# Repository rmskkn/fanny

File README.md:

# Fanny — a USB PWM fan controller

A USB-controlled carrier board for an STM32F103C8T6 "Blue Pill" module. It
drives four 12 V PC fans and reads four analog sensors. The module shows up
on the host as a USB CDC serial port (`/dev/ttyACM*` or `COMx`).

## Key features

- **4 independent fan channels.** Each one switches between `pwm` (4-pin
  signal control) and `dc` (3-pin supply chopping) at runtime.
- **4 analog inputs** for NTC or voltage sensors plus 12 V rail sensing. All
  share one ADC scan with mV conversion.
- **Tach and stall detection** on all 4 channels. Fans 1-3 are counted by
  hardware timers, fan 4 by a level-checked interrupt.
- **Hardware failsafe by design.** Every control line rests in its "fan on"
  state by default, held there by pull resistors alone. A fan runs at
  100% on power-up, after a crash, or with the MCU pulled out. No firmware
  or host required.
- **Text protocol over USB CDC.** Comes with a Python CLI (`fanctl.py`) and
  a daemon (`fancontrold.py`) for temperature or GPU-temperature curves.

## Repository structure

```
.
├── firmware/          MCU firmware
│   ├── Core/          clocks, SysTick, linker script, board pin map
│   ├── Drivers/       libopencm3 submodule
│   ├── USB_DEVICE/    USB CDC-ACM device
│   ├── App/           fan, pwm, tach, protocol, thermal, safety
│   └── tests/         host-side unit tests
├── hardware/
│   ├── kicad/         schematic, symbol lib, board
│   ├── case/          3D-printed tray and cover (FreeCAD script, STEP, STL, renders)
│   ├── bom.csv        bill of materials
│   ├── pcb_3d.png     3D render of the placed board
│   ├── pcb_top.png    placement plot seen from the top
│   └── datasheets/    links to the key datasheets
└── host/              fanctl.py command-line client (pyserial)
```

## Prerequisites

KiCad 10.0.7, arm-none-eabi-gcc, OpenOCD, and Python 3 with pyserial:

```sh
# Arch
sudo pacman -S kicad arm-none-eabi-gcc arm-none-eabi-newlib openocd python python-pyserial

# Ubuntu 24.04
sudo add-apt-repository ppa:kicad/kicad-10.0-releases
sudo apt update
sudo apt install kicad gcc-arm-none-eabi openocd python3 python3-serial
```

You also need an ST-Link V2 programmer wired to the Blue Pill's SWD header
to flash firmware. FreeCAD 1.1 is only needed to change the printed case.

`make analyze` (clang static analyzer over the firmware, see Build below)
needs clang-23 specifically; a different major version can enable a
different default set of checkers, which has produced false positives on
this codebase before.

```sh
# Arch: clang already provides a clang-23 symlink, nothing extra to install
sudo pacman -S clang

# Ubuntu 24.04: its own archives don't carry clang-23, so use the LLVM
# project's own installer instead
wget https://apt.llvm.org/llvm.sh
chmod +x llvm.sh
sudo ./llvm.sh 23
```

## Hardware design

### Block overview

```mermaid
flowchart TB
    classDef power fill:#fde3d8,stroke:#e2572b,color:#111
    classDef usb fill:#dbe7ff,stroke:#2f6fed,color:#111
    classDef mcu fill:#e8d7f5,stroke:#5b4b8a,color:#111
    classDef pwm fill:#d7f5df,stroke:#2f9e44,color:#111
    classDef dcmode fill:#fdecc3,stroke:#c77f00,color:#111
    classDef tach fill:#d7f5df,stroke:#0f9b8e,color:#111
    classDef analog fill:#fbd9e8,stroke:#c2255c,color:#111

    subgraph PWR["Power 12 V"]
        PSU["12 V PSU"] --> J1["J1 Mate-N-Lok"] --> F1["F1 PTC 2.5A"] --> D2["D2 Schottky"] --> V12["+12V"]
        V12 --> FANV["fan +12V x4"]
        V12 --> DIV["10k/3.3k divider"] --> PB0["PB0 ADC"]
        V12 --> D3["D3 1N4148WT"] --> U1["U1 AMS1117-3.3"]
    end

    subgraph USB3V3["USB / 3V3"]
        USB["USB via Blue Pill microB"] --> P5V["+5V"] --> LDO["Blue Pill LDO"] --> V33["+3V3"] --> FB1["FB1"] --> V33A["+3V3A"]
        U1 --> V33
    end

    subgraph MCU["Blue Pill module on J2 and J3"]
        subgraph PWMSIG["PWM signal on fan pin 4"]
            TIM4["TIM4 PB6..PB9 25kHz"] --> BSS["BSS138 open drain"] --> FPWM["fan PWM pin"]
        end
        subgraph DCMODE["DC-mode motor switch per channel"]
            QINV["Q_inv BSS138"] --> QEN["Q_en gated by FANn_DCEN"] --> QPNP["Q_pnp AO3401A pull-up"] --> QHS["Q_hs AO3401A"] --> FSW["fan +12V motor switch"]
            GPIO["PA6 PA7 PA8 PB1 GPIO"] --> QEN
        end
        TIM4 -. reuses PWM signal .-> QINV
        subgraph TACHLANE["Tach"]
            FT["fan tach"] --> PU["10k pull-up"] --> RC["RC filter"] --> EXTI["TIM1/2/3 counters, EXTI PB15"]
        end
    end

    subgraph ANALOG["Analog inputs"]
        SENS["sensors"] --> RCB["1k + 100n + BAT54S"] --> ADC["PA0..PA3 ADC x4"]
    end

    class PSU,J1,F1,D2,V12,FANV,DIV,D3,U1 power
    class PB0 mcu
    class USB,P5V,LDO,V33,FB1,V33A usb
    class TIM4,BSS,FPWM pwm
    class QINV,QEN,QPNP,QHS,FSW,GPIO dcmode
    class FT,PU,RC,EXTI tach
    class SENS,RCB,ADC analog
```

### Pin map

| Function | Pins | Peripheral |
|---|---|---|
| Fan 1–4 PWM signal and the motor-switch chop signal in DC mode | PB6 PB7 PB8 PB9 | TIM4 CH1–4 at 25 kHz |
| Fan 1–4 DC-mode enable | PA6 PA7 PA8 PB1 | plain push-pull GPIO |
| Fan 1–3 tach | PA9 PA15 PB5 | TIM1 CH2, TIM2 CH1 (partial remap 1), TIM3 CH2 (partial remap), each in external clock mode counting falling edges in hardware |
| Fan 4 tach | PB15 | EXTI15 on both edges, counted only on a real high-to-low level change |
| AIN1–AIN4 | PA0–PA3 | ADC1 IN0–IN3 |
| 12 V sense | PB0 | ADC1 IN8 |

### Compatibility

Verified against the [Intel 4-wire PWM fan spec rev 1.2](https://www.konilabs.net/docs/standards/fan/intel_4wire_pwm_fans_specs_rev1_2.pdf):

| Spec requirement | Board implementation | Status |
|---|---|---|
| Pinout of GND then +12 V then tach then PWM | `Fan_4pin` header wired in that order | Match |
| PWM must be open-drain or open-collector with the fan pulling up | BSS138 open-drain transistor where the MCU only sinks | Match |
| PWM frequency between 21 kHz and 28 kHz with 25 kHz nominal | TIM4 at 72 MHz / 2880 which is exactly 25.000 kHz | Match |
| A released PWM line must run the fan at full speed | 100 kΩ pull-down holds the transistor off until firmware drives it | Match |
| Tach must be open-collector and pulled up at 2 pulses per rev | 10 kΩ pull-up to 3.3 V with `TACH_PULSES_PER_REV = 2` in firmware | Match |
| Tach pull-up rail of 5 V or less into a tolerant input | Pulled to 3.3 V. PA9, PA15 and PB15 are 5 V tolerant; PB5 is not, so fan 3 needs the 3.3 V pull-up | Match |

### Analog inputs (AIN1–AIN4)

Each input is a 3-pin header carrying 3V3A and SIG and GND. The conditioning
chain works like this:

- A 10 kΩ pull-up to 3V3A. Together with a 10 kΩ NTC to GND it forms a
  ratiometric temperature divider. Leave it unfitted for voltage-output
  sensors.
- A 1 kΩ series resistor and 100 nF to GND for anti-aliasing and sample
  charge.
- A BAT54S clamp to GND and 3V3A. PA0–PA3 are **not** 5 V tolerant.

The ADC references VDDA. The firmware measures VREFINT so it can report
millivolts corrected for the actual supply voltage.

#### Choosing an NTC

The on-board pull-up is 10 kΩ, matched to a 10 kΩ NTC with B=3950 (`ntc_r25 =
10000`, `ntc_beta = 3950` in the fan daemon config, both already the
defaults). Any bare 2-wire 10 kΩ/B3950 probe plugs straight in, SIG and GND,
no third wire needed — this is what the probe bundled with the
[Skip0ner 1X4L fan-1248 conf v1](https://skiponer.com/1x4l-pwm-fan-controller-manual/)
module is. Expected mV at a given temperature:
`hardware/datasheets/NTC-10k-B3950 Response Curve.md`, taken from the
10k/3950 column of Focusensing's
[10k thermistor reference chart](https://www.focusensing.com/10k-thermistor-chart-type-2-vs-type-3-vs-3950-tables_n196).
The onboard autocurve mode (`auto on`) uses the same table, baked into
`firmware/App/ntc_calib.h`. The firmware saves `auto on` or `auto off` to
flash with the curves, so a board that reboots without a host comes back in
the same mode.

A different R25 needs a matching pull-up swap, since the pull-up sets both
the divider's output range and the firmware's calibration constant: match
`ntc_r25` (host) and `ntc_calib_ain1..4` (firmware) to the new part's R25 and
B, and re-check `fanctl.py get`'s `ain N mv` against a known temperature
before trusting the curve.

### Power

- **12 V input:** a screw terminal, a PTC that holds 2.5 A, then an SS54
  Schottky diode (anode toward the PTC) that blocks a reversed supply instead
  of tripping the PTC. The PTC resets on its own, so a miswire leaves nothing
  to replace.
- **Module supply:** USB, 12 V, or both. The LDO on the Blue Pill makes
  3.3 V from USB VBUS. U1 (AMS1117-3.3) on the carrier makes 3.3 V from the
  12 V bus and feeds the module 3V3 pin, so the board runs with no USB cable.
  With both present, whichever regulator sits a little higher carries the
  load. D3 sits in front of U1 so that a USB-only board doesn't back-feed
  3.3 V onto the 12 V bus through U1.
- **12 V monitoring:** a 10 kΩ/3.3 kΩ divider into PB0. Full scale lands near
  13.3 V, so a supply above that reads as 13.3 V.
- **USB:** the micro-B connector of the Blue Pill and nothing else. The
  carrier has no USB connector or header or ESD protection of its own. The
  firmware pulls D+ low for 10 ms at boot to force the host to re-enumerate.

## BOM list

The full bill of materials is in [`hardware/bom.csv`](hardware/bom.csv).

## Case

[`hardware/case/`](hardware/case/) holds a two-part printed case: a low tray
and a cover. Both parts print without supports and weigh about 33 g together
in PLA.

The PCB screws onto four standoffs in the tray with M2x6 self-tapping screws.
Fit the MH4 screw before you plug in the Blue Pill, because the module covers
it. The tray wall stands 2 mm above the board, so the tray works on its own
too.

The cover sits on the tray wall, and a lip inside the wall holds it by
friction. Each fan header gets a window wide enough for a finger on the plug
latch. More windows sit over the sensor inputs, the 12 V input and the Blue
Pill SWD pins, and a notch in the side leaves room for the USB plug.

All sizes are constants at the top of `fan_controller_case.py`. After you
change one, rebuild the FreeCAD document, the STEP files and the STLs:

```sh
cd hardware/case
freecadcmd fan_controller_case.py
```

Run `freecad fan_controller_case.py` instead to also redraw the two images
above. The FreeCAD window opens for a few seconds and closes on its own.

The cover underside sits 20 mm above the PCB. That figure comes from an
estimated 18.6 mm Blue Pill stack with the BOOT jumpers fitted, so measure
your module and raise `TOP_CLEAR` if it stands taller.

## Firmware

### Build

```sh
git clone --recurse-submodules git@github.com:rmskkn/fanny.git
cd fanny
make                 # firmware/build/fanny.elf, .bin (~11.5 KiB flash)
make flash           # flash fanny.bin, OpenOCD + ST-Link over SWD
make test            # host-side protocol and conversion tests
make analyze         # clang static analyzer over the firmware sources
```

The first `make` builds libopencm3 for STM32F1 only. It also runs
`git submodule update --init` when the clone has no submodule checkout. The
same targets work from inside `firmware/`.

`make flash` wraps this OpenOCD call, with an ST-Link programmer on the
Blue Pill's SWD header. `fanny.bin` is a raw image with no load address, so
one is given on the command line, the start of flash on this MCU:

```sh
openocd -f interface/stlink.cfg -f target/stm32f1x.cfg \
    -c "program firmware/build/fanny.bin verify reset exit 0x08000000"
```

`fanny.elf` still builds alongside it (`make` keeps producing both), kept
for `arm-none-eabi-size` and debugging, but flashing only ever needs the bin.

### Failsafe behaviour

All fans run at 100 % whenever the controller is not in control and that holds
in both `pwm` and `dc` mode. Fan power comes straight from 12 V so this needs
nothing but 12 V present. The PWM signal line and the motor switch and the
DC-mode enable all rest in their "fan on" state. Pin 4 is released and
`R_gpd` holds the motor switch on and `R_dcen` holds the enable off. Either
mode reaches 100 % the same way.

| Case | Result |
|---|---|
| Power-up before the first command from the host, `auto off` saved | 100 % at reset, then the curve fallback below within 1 s |
| Power-up with `auto on` saved | Each fan follows its temperature curve from boot, with or without a host |
| USB unplugged or host powered off, `auto on` | Module stays powered from 12 V through U1 and keeps driving each fan from its temperature curve |
| USB unplugged or host powered off, `auto off` | Module stays powered from 12 V through U1, gets no commands, and after 20 s falls back to the curves as in the last row |
| Module pulled out of its socket | Both switches rest on at 100 % |
| Supply sags below the reset threshold of the STM32 near 1.9 V | MCU held in reset and both switches rest on at 100 % |
| Firmware hangs | Watchdog resets the MCU after 1 s and both switches rest on during reset at 100 % |
| No valid command for 20 s while the module is still powered and `auto off` | Firmware failsafe sets 100 %, the LED blinks fast and the mode stays unchanged. Within 1 s each fan falls back to its saved curve. A channel with no curve or a bad sensor stays at 100 %, and a corrupted curve on any channel keeps every fan at 100 %. The next valid command hands control back to the host |

Running `fanctl.py watch` or a control daemon keeps the 20 s timer from
expiring. A fan is flagged `stall=1` when its duty sits above 0 but its tach
reads 0 RPM for 3 s. Fans without a tach wire always show this flag.

### Host commands

The protocol is text over USB CDC and the baud rate is ignored. Each command
is one line ending in `\n` and each reply ends with `ok` or `err <reason>`.

```
> set 2 40          duty 0..100 for fan 1..4 or "all"
ok
> mode 3 dc         pwm (4-pin) | dc (3-pin)
ok
> get
fan 1 mode=pwm duty=100 rpm=1590 stall=0
fan 2 mode=pwm duty=40 rpm=780 stall=0
fan 3 mode=dc duty=100 rpm=1200 stall=0
fan 4 mode=pwm duty=100 rpm=0 stall=1
ain 1 raw=2047 mv=1649
...
v12 mv=12043
vdda mv=3302
mcu temp=31.4
failsafe=0
ok
> ping              keepalive
ok
```

## Host tool

```sh
pip install -r host/requirements.txt
python3 host/fanctl.py -p /dev/ttyACM0 get
python3 host/fanctl.py set all 50
python3 host/fanctl.py mode 3 dc
python3 host/fanctl.py watch -i 2
```

### Setting one fan

Use the fan number from 1 to 4 in place of `all`. Fan 1 is header J5 and fan
4 is header J8.

```sh
python3 host/fanctl.py set 1 50      # fan 1 to 50 %
python3 host/fanctl.py set 3 80      # fan 3 to 80 %
python3 host/fanctl.py set 4 0       # fan 4 to 0 % (some fans keep turning slowly)
python3 host/fanctl.py -p /dev/ttyACM1 set 2 40   # board on another port
```

- Each command sets one fan or all fans. Lists such as `1,2` and ranges such
  as `1-3` are not accepted.
- To check a fan run `python3 host/fanctl.py get` and read the
  `fan N mode=... duty=... rpm=...` line.
- With `auto off`, settings hold only while the host keeps talking to the
  board. When no command arrives for 20 s the fans fall back to the saved
  curves, or 100 % without them. Keep `fanctl.py watch` or a control daemon
  running to hold the values.
- `mode <1-4|all> pwm|dc` picks the speed-control path for a channel: `pwm`
  for a 4-pin fan, `dc` for a 3-pin fan. It falls back to `pwm` at every
  boot and after every reconnect so the channel of a 3-pin fan needs
  `mode N dc` sent again each time.

The `FanController` class in `fanctl.py` can be imported to build a control
daemon. One example is a daemon that maps an NTC reading from `ain` onto a fan
duty. For a 10 kΩ NTC sitting on the 10 kΩ bias resistor the resistance is
R<sub>NTC</sub> = 10 kΩ × mV / (VDDA − mV).

### Fan control daemon

`host/fancontrold.py` is exactly that daemon. It reads an INI config shown in
`host/fancontrol.conf.example`. The config can set each of the four channels
to a constant duty or to a temperature curve driven by one AIN input or to a
curve driven by the temperature of an NVIDIA GPU through `sensor = gpuN` read
via `nvidia-smi` using the higher of the core and memory temperature. A
managed channel also takes `type = pwm` for the 4-pin default or `type = dc`
for a 3-pin fan. The daemon sends `mode` once at startup and again after every
reconnect because a firmware reset returns every channel to `pwm`. It sends
`auto off` at the same points, because the board ignores `set` while `auto on`
runs. Stopping the daemon leaves the board in `auto off`, so run
`fanctl.py auto on` to hand control back to the board. Every cycle
it re-sends the duty of each managed channel which doubles as the ping that
holds off the 20 s firmware failsafe. A channel with no `[fanN]` section is
left alone. `nvidia-smi` must be on `PATH` and no extra Python dependency is
needed.

For a `gpuN` sensor install the proprietary NVIDIA driver which provides
`nvidia-smi`:

```sh
# Arch
sudo pacman -S nvidia nvidia-utils

# Ubuntu 24.04
sudo apt install nvidia-driver-550
```

Reboot the machine to load the nvidia modules. Verify with
`nvidia-smi --query-gpu=index,temperature.gpu,temperature.memory --format=csv`.

```sh
cp host/fancontrol.conf.example ~/.config/fancontrol.conf
# edit ~/.config/fancontrol.conf for your sensors and curves
python3 host/fancontrold.py                 # foreground, Ctrl-C to stop
```

To run it as a systemd user service:

```sh
mkdir -p ~/.config/systemd/user
cp host/systemd/fancontrold.service ~/.config/systemd/user/
# edit ExecStart in that file to this repo's checkout path
systemctl --user daemon-reload
systemctl --user enable --now fancontrold.service
loginctl enable-linger "$USER"   # only if the board must run with no user session logged in
```

### Updating firmware via USB

A fresh board's first flash still needs SWD: `make ota_fw` builds the
bootloader and app, `make flash_ota` writes the app part at its fixed
address (the bootloader itself has no `make` target yet, so it still
needs its own manual OpenOCD `program` command). From there, every
later update goes over the same USB CDC link, no SWD needed.

```sh
python3 host/fwtool.py flash firmware/build/fanny_app.bin -v 2
```

This sends `update` to the running app, which reboots into the bootloader.
The bootloader erases the app region, writes the new image, checks its
SHA-256, and boots it. `-v` sets the version number sealed into the image;
bump it on every release. To build the sealed image without flashing it:

```sh
python3 host/fwtool.py build firmware/build/fanny_app.bin -v 2 -o update.img
```

The image format `fwtool.py` builds, and the bootloader checks, comes from
the `firmware/Bootloader/chunky` submodule
([rmskkn/chunky_mcu_updater](https://github.com/rmskkn/chunky_mcu_updater)).

## Known limits

- **0 % doesn't stop every 4-pin fan in `pwm` mode** (fan-dependent). It does
  stop the fan in `dc` mode.
- **Duty 1-100 % maps to 10-100 % on the PWM line.** A Noctua NF-P12 PWM
  won't start below 10 % and stops below about 6 % even after a spin-up, so
  the firmware never sends less than 10 % unless you set 0 %. At 1 % that fan
  runs at about 200 rpm. Every other setting lands a little above its raw
  value: 50 % sends 55 %.
- **3-pin fans in `dc` mode won't start below ~30-40 % duty** (motor limit,
  not firmware). Set a curve minimum above it.
- **Fan 4 tach uses an interrupt, not a hardware counter.** Each counter
  needs a whole timer, and the STM32F103C8 has four: TIM1-TIM3 count fans
  1-3 and TIM4 makes the PWM. Fan 4 runs on EXTI15 with a pin-level check
  that ignores spikes shorter than the interrupt entry time (about 0.5 us).
  Longer glitches still count, and edges closer together than the handler
  runtime can merge.
- **JTAG is off** because fan 2 tach uses PA15. SWD on PA13/PA14 still
  flashes and debugs the board.
- **Tach under-reads in `dc` mode** since the fan is unpowered during the
  chopped-off phase. `stall` is only meaningful near 100 % duty.
- **25 kHz chop stresses a fan's input cap** but stays inaudible. All four
  `pwm` channels share one chop frequency.

## Special thanks

These open-source projects helped build the project:

1. [KiCAD-MCP-Server](https://github.com/mixelpixx/KiCAD-MCP-Server) by
   mixelpixx drives KiCad schematic and PCB edits over MCP.
2. [freecad-mcp](https://github.com/neka-nat/freecad-mcp) by neka-nat drives
   FreeCAD over MCP for the printed case.
3. [KiCadRoutingTools](https://github.com/drandyhaas/KiCadRoutingTools) by
   drandyhaas reroutes nets that fail DRC.

## License

Copyright © 2026 Roman Skakun.

The hardware and the code use different licenses.

The hardware design files in `hardware/` (KiCad project, BOM, renders, and
the case model files) are licensed under
[Creative Commons Attribution-NonCommercial-ShareAlike 4.0 International](LICENSE)
(CC BY-NC-SA 4.0). You may build, modify and share the design for personal
and other non-commercial purposes, with attribution and under the same
license. Commercial use needs a separate written license from the copyright
holder. That includes selling assembled boards, bare PCBs or kits.

The 3D models in `hardware/kicad/3dmodels/` are copied from the KiCad
library and keep their own CC-BY-SA 4.0 license with the KiCad libraries
exception. See [`hardware/kicad/3dmodels/README.md`](hardware/kicad/3dmodels/README.md).

The code in `firmware/`, `host/`, `scripts/`, `hardware/scripts/` and the
case generator `hardware/case/fan_controller_case.py` is licensed under the [GNU General Public License v3.0](LICENSE-GPL-3.0). You
may use, change and redistribute it, including commercially, as long as you
release the source of every version you distribute under the same license.

`firmware/Drivers/libopencm3` is a submodule under its own LGPL-3.0 license
and is covered by neither of the above.

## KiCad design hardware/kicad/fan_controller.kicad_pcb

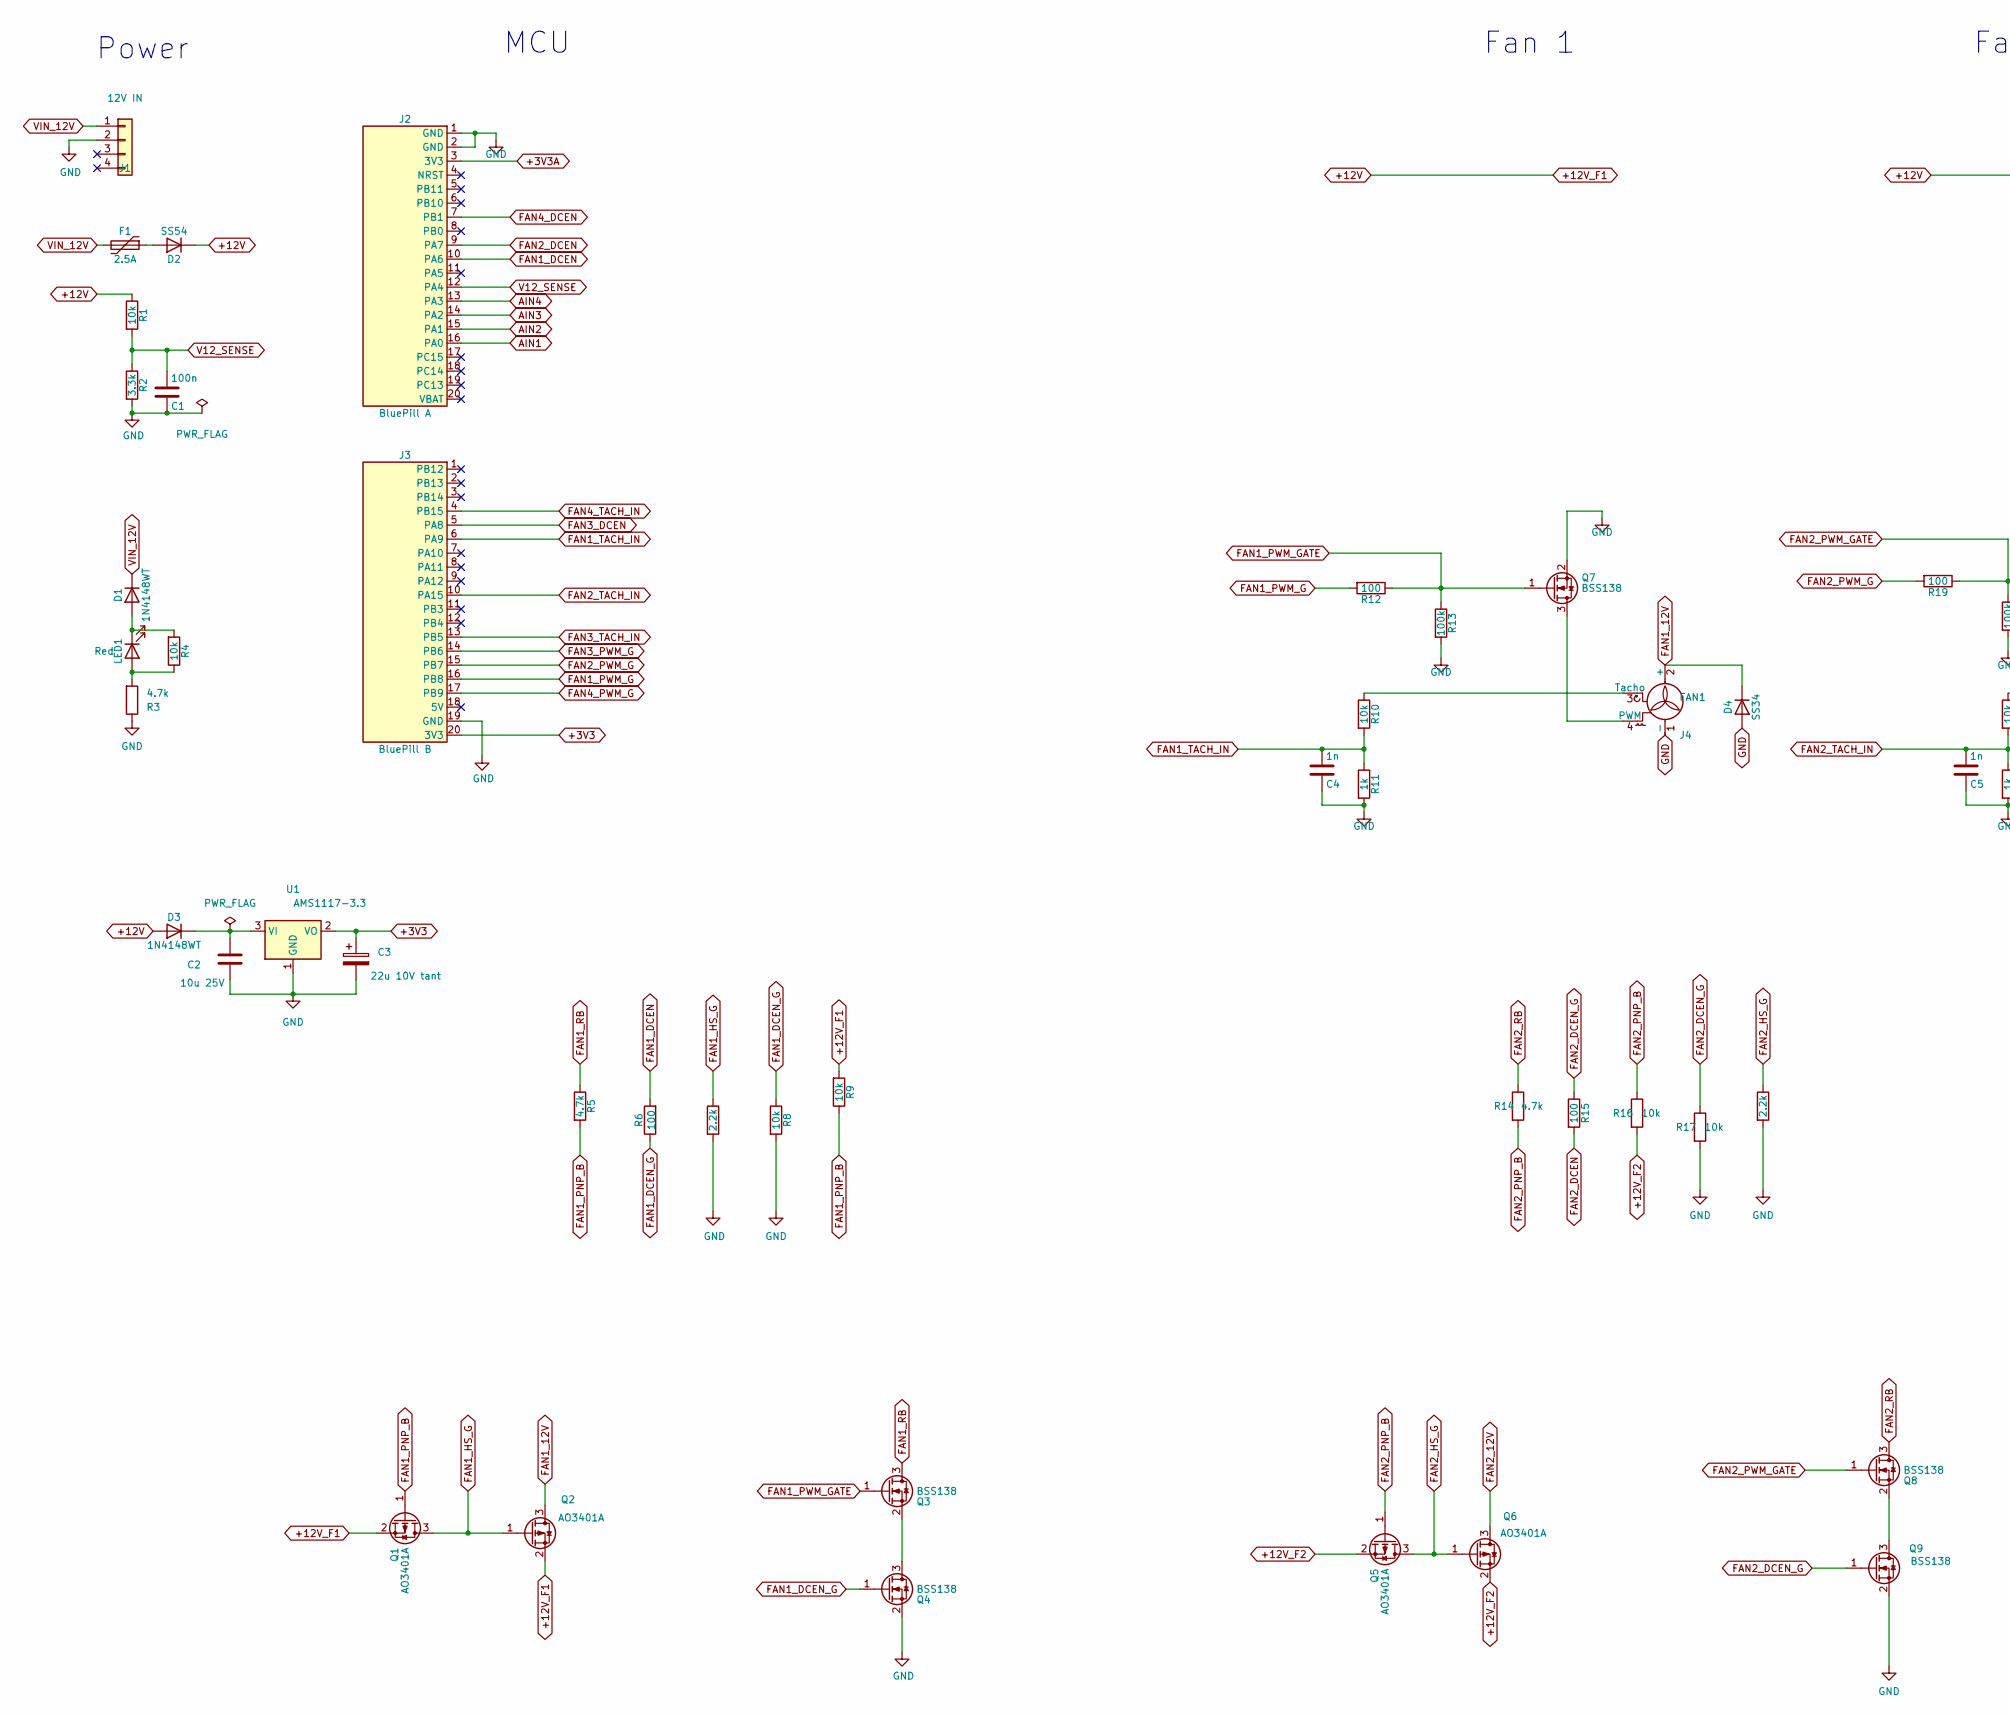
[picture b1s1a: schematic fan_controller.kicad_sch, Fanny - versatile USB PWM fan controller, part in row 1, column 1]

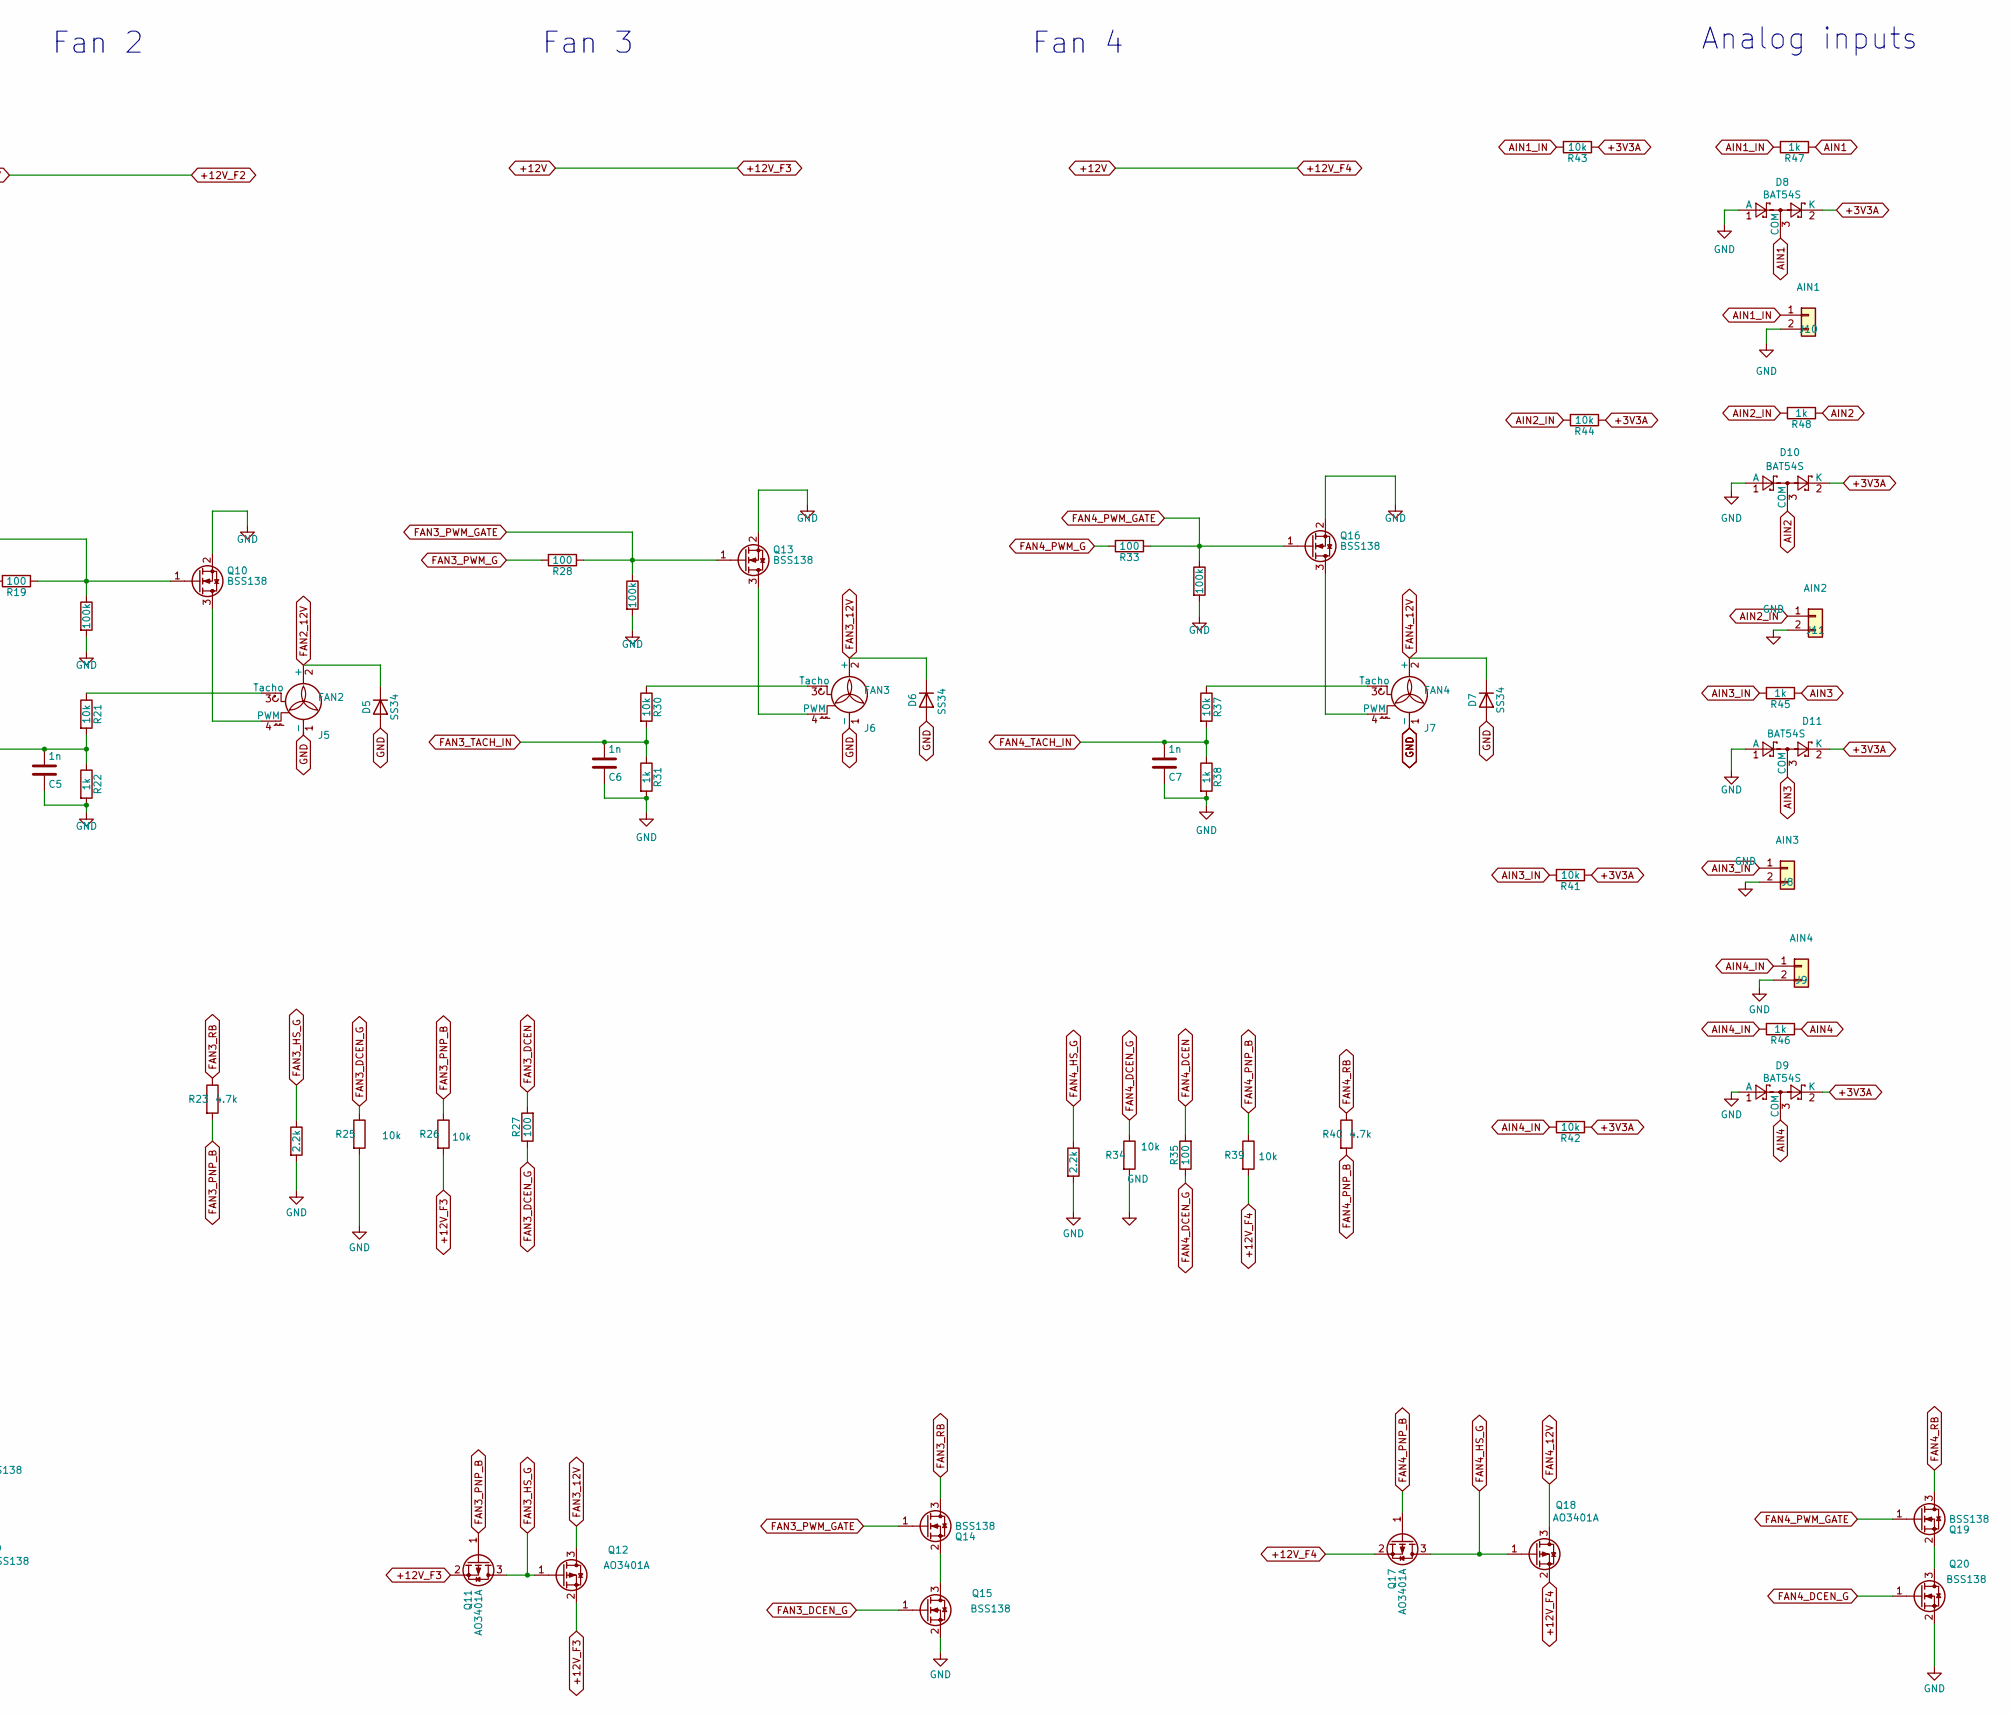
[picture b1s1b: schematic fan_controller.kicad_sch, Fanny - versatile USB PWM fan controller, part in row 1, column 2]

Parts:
C1: 100n; C_0603_1608Metric
C2: 10u 25V; C_0805_2012Metric
C3: 22u 10V tant; CP_EIA-3216-18_Kemet-A
C4, C5, C6, C7: 1n; C_0603_1608Metric
D1, D3: 1N4148WT; D_SOD-523
D2: SS54; D_SMB; MPN Littelfuse SMBJ13A
D4, D5, D6, D7: SS34; D_SMA; MPN SS34
D8, D9, D10, D11: BAT54S; SOT-23; MPN Nexperia BAT54S,215
F1: 2.5A; Fuse_1812_4532Metric; MPN Bourns MF-MSMF250/16X-2
J1: 12V IN; ConnHeader_MateNLok_1x04_P5.08mm_Vertical; MPN TE Connectivity 350424-1
J2: BluePill A; PinSocket_1x20_P2.54mm_Vertical
J3: BluePill B; PinSocket_1x20_P2.54mm_Vertical
J4: FAN1; FanPinHeader_1x04_P2.54mm_Vertical; MPN Molex 47053-1000
J5: FAN2; FanPinHeader_1x04_P2.54mm_Vertical; MPN Molex 47053-1000
J6: FAN3; FanPinHeader_1x04_P2.54mm_Vertical; MPN Molex 47053-1000
J7: FAN4; FanPinHeader_1x04_P2.54mm_Vertical; MPN Molex 47053-1000
J8: AIN3; JST_PH_B2B-PH-K_1x02_P2.00mm_Vertical
J9: AIN4; JST_PH_B2B-PH-K_1x02_P2.00mm_Vertical
J10: AIN1; JST_PH_B2B-PH-K_1x02_P2.00mm_Vertical
J11: AIN2; JST_PH_B2B-PH-K_1x02_P2.00mm_Vertical
LED1: Red; LED_0603_1608Metric
Q1, Q2, Q5, Q6, Q11, Q12, Q17, Q18: AO3401A; SOT-23; MPN Alpha & Omega AO3401A
Q3, Q7, Q8, Q10, Q13, Q14, Q16, Q19: BSS138; SOT-23; MPN onsemi BSS138
Q4, Q9, Q15, Q20: BSS138; SOT-23
R1, R4, R8, R9, R10, R16, R17, R21, R25, R26, R30, R34, R37, R39, R41, R42, R43, R44: 10k; R_0603_1608Metric
R2: 3.3k; R_0603_1608Metric
R3: 4.7k; R_1206_3216Metric
R5, R14, R23, R40: 4.7k; R_0603_1608Metric
R6, R12, R15, R19, R27, R28, R33, R35: 100; R_0603_1608Metric
R7, R18, R24, R32: 2.2k; R_0603_1608Metric
R11, R22, R31, R38, R45, R46, R47, R48: 1k; R_0603_1608Metric
R13, R20, R29, R36: 100k; R_0603_1608Metric
U1: AMS1117-3.3; SOT-223-3_TabPin2

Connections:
+3V3: C3.1, J3.20 (3V3), U1.2 (VO); also elsewhere on the board
+3V3A: D8.2 (K), D9.2 (K), D10.2 (K), D11.2 (K), J2.3 (3V3), R41.1, R42.1, R43.1, R44.1; also elsewhere on the board
+12V: D2.1 (K), D3.2 (A), Q1.2 (S), Q2.2 (S), Q5.2 (S), Q6.2 (S), Q11.2 (S), Q12.2 (S), Q17.2 (S), Q18.2 (S), R1.1, R9.2, R16.2, R26.2, R39.2
AIN1: D8.3 (COM), J2.16 (PA0), R47.1
AIN1_IN: J10.1, R43.2, R47.2
AIN2: D10.3 (COM), J2.15 (PA1), R48.1
AIN2_IN: J11.1, R44.2, R48.2
AIN3: D11.3 (COM), J2.14 (PA2), R45.1
AIN3_IN: J8.1, R41.2, R45.2
AIN4: D9.3 (COM), J2.13 (PA3), R46.1
AIN4_IN: J9.1, R42.2, R46.2
FAN1_12V: D4.1 (K), J4.2 (+), Q2.3 (D)
FAN1_DCEN: J2.10 (PA6), R6.2
FAN1_DCEN_G: Q4.1 (G), R6.1, R8.1
FAN1_HS_G: Q1.3 (D), Q2.1 (G), R7.1
FAN1_PNP_B: Q1.1 (G), R5.2, R9.1
FAN1_PWM_G: J3.16 (PB8), R12.2
FAN1_PWM_GATE: Q3.1 (G), Q7.1 (G), R12.1, R13.1
FAN1_RB: Q3.3 (D), R5.1
FAN1_TACH_IN: C4.1, J3.6 (PA9), R10.2, R11.1
FAN2_12V: D5.1 (K), J5.2 (+), Q6.3 (D)
FAN2_DCEN: J2.9 (PA7), R15.2
FAN2_DCEN_G: Q9.1 (G), R15.1, R17.1
FAN2_HS_G: Q5.3 (D), Q6.1 (G), R18.1
FAN2_PNP_B: Q5.1 (G), R14.2, R16.1
FAN2_PWM_G: J3.15 (PB7), R19.2
FAN2_PWM_GATE: Q8.1 (G), Q10.1 (G), R19.1, R20.1
FAN2_RB: Q8.3 (D), R14.1
FAN2_TACH_IN: C5.1, J3.10 (PA15), R21.2, R22.1
FAN3_12V: D6.1 (K), J6.2 (+), Q12.3 (D)
FAN3_DCEN: J3.5 (PA8), R27.2
FAN3_DCEN_G: Q15.1 (G), R25.1, R27.1
FAN3_HS_G: Q11.3 (D), Q12.1 (G), R24.1
FAN3_PNP_B: Q11.1 (G), R23.2, R26.1
FAN3_PWM_G: J3.14 (PB6), R28.2
FAN3_PWM_GATE: Q13.1 (G), Q14.1 (G), R28.1, R29.1
FAN3_RB: Q14.3 (D), R23.1
FAN3_TACH_IN: C6.1, J3.13 (PB5), R30.2, R31.1; also elsewhere on the board
FAN4_12V: D7.1 (K), J7.2 (+), Q18.3 (D)
FAN4_DCEN: J2.7 (PB1), R35.2
FAN4_DCEN_G: Q20.1 (G), R34.1, R35.1
FAN4_HS_G: Q17.3 (D), Q18.1 (G), R32.1
FAN4_PNP_B: Q17.1 (G), R39.1, R40.2
FAN4_PWM_G: J3.17 (PB9), R33.2
FAN4_PWM_GATE: Q16.1 (G), Q19.1 (G), R33.1, R36.1
FAN4_RB: Q19.3 (D), R40.1
FAN4_TACH_IN: C7.1, J3.4 (PB15), R37.2, R38.1; also elsewhere on the board
GND: C1.2, C2.2, C3.2, C4.2, C5.2, C6.2, C7.2, D4.2 (A), D5.2 (A), D6.2 (A), D7.2 (A), D8.1 (A), D9.1 (A), D10.1 (A), D11.1 (A), J1.2, J2.1 (GND), J2.2 (GND), J3.19 (GND), J4.1 (-), J5.1 (-), J6.1 (-), J7.1 (-), J8.2, J9.2, J10.2, J11.2, Q4.2 (S), Q7.2 (S), Q9.2 (S), Q10.2 (S), Q13.2 (S), Q15.2 (S), Q16.2 (S), Q20.2 (S), R2.2, R3.1, R7.2, R8.2, R11.2, R13.2, R17.2, R18.2, R20.2, R22.2, R24.2, R25.2, R29.2, R31.2, R32.2, R34.2, R36.2, R38.2, U1.1 (GND); also elsewhere on the board
unnamed: D1.2 (A), LED1.1 (K), R4.2
unnamed: D2.2 (A), F1.1
unnamed: C2.1, D3.1 (K), U1.3 (VI)
unnamed: J4.4 (PWM), Q7.3 (D)
unnamed: J4.3 (Tacho), R10.1
unnamed: J5.4 (PWM), Q10.3 (D)
unnamed: J5.3 (Tacho), R21.1
unnamed: J6.4 (PWM), Q13.3 (D)
unnamed: J6.3 (Tacho), R30.1
unnamed: J7.4 (PWM), Q16.3 (D)
unnamed: J7.3 (Tacho), R37.1
unnamed: LED1.2 (A), R3.2, R4.1
unnamed: Q3.2 (S), Q4.3 (D)
unnamed: Q8.2 (S), Q9.3 (D)
unnamed: Q14.2 (S), Q15.3 (D)
unnamed: Q19.2 (S), Q20.3 (D)
V12_SENSE: C1.1, J2.12 (PA4), R1.2, R2.1
VIN_12V: D1.1 (K), F1.2, J1.1

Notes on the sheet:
Analog inputs
Power
Fan 3
MCU
Fan 2
Fan 1
Fan 4

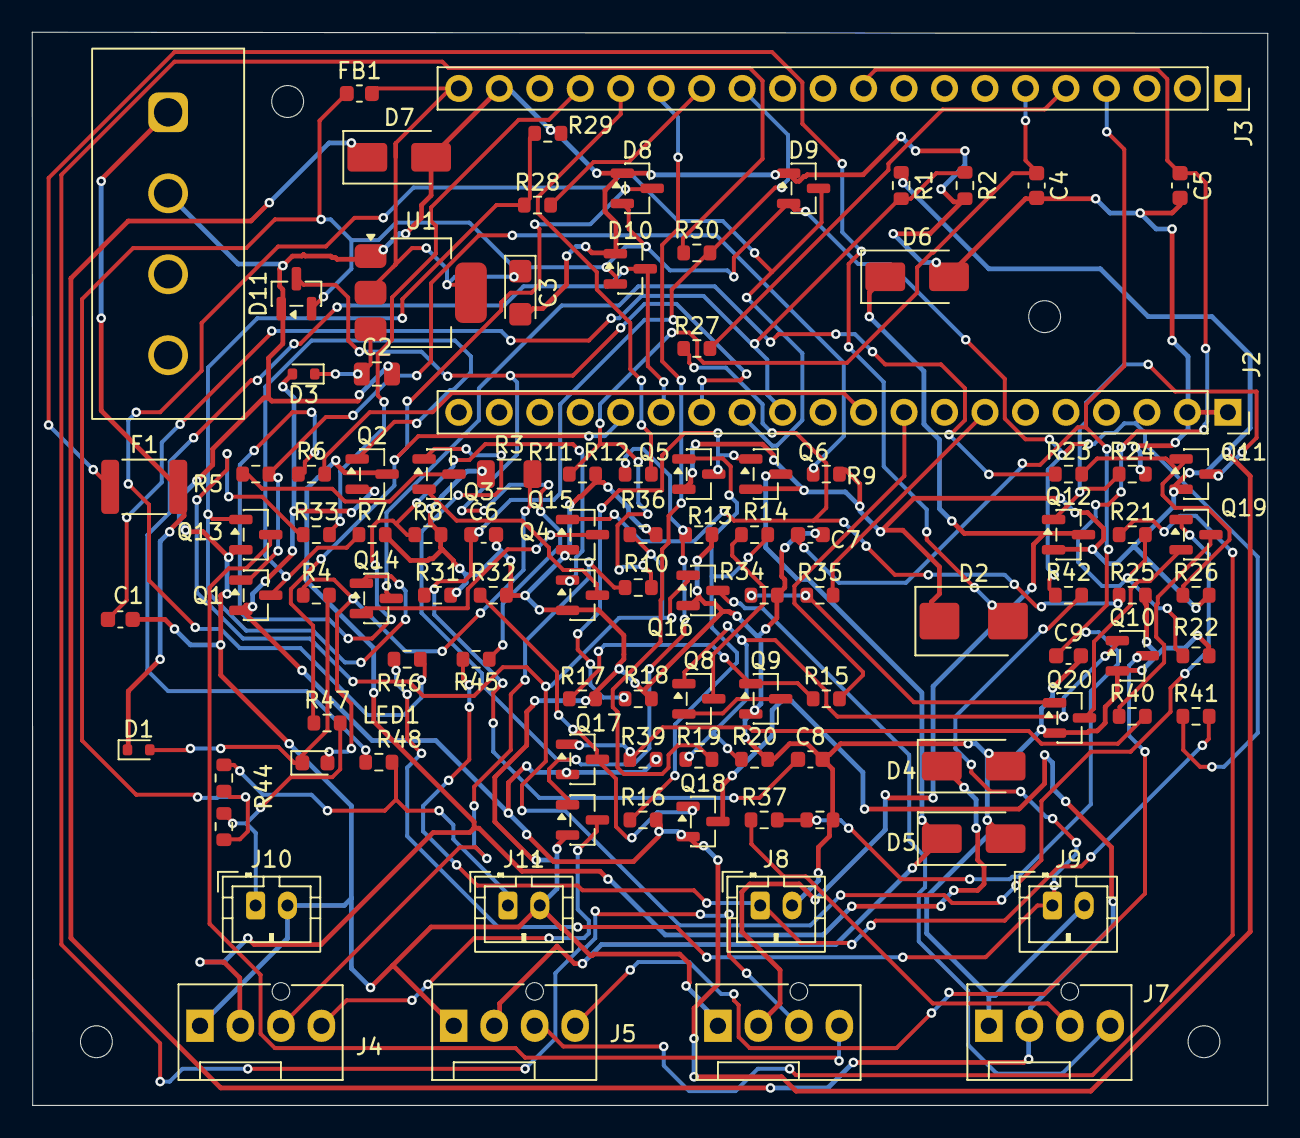
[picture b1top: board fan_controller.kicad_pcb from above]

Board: 2 copper layers, 77.5 x 67.3 mm, 107 parts (0 on the bottom side), 66 nets.

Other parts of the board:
C8, C9: 1n; C_0603_1608Metric
FB1: 600R@100MHz; L_0603_1608Metric
MH1, MH2, MH3, MH4: MountingHole_2mm

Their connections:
+3V3: FB1.2; also elsewhere on the board
+3V3A: FB1.1; also elsewhere on the board
FAN3_TACH_IN: C8.1; also elsewhere on the board
FAN4_TACH_IN: C9.1; also elsewhere on the board
GND: C8.2, C9.2; also elsewhere on the board

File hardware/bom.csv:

Qty,References,Value,Footprint,MPN (example),DigiKey PN,DigiKey URL,Notes,DNP
1,C1,100n,C_0603_1608Metric,Yageo CC0603KRX7R9BB104,311-1344-2-ND,https://www.digikey.com/en/products/detail/yageo/CC0603KRX7R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,,
4,C4 C5 C6 C7,1n,C_0603_1608Metric,Yageo CC0603KRX7R9BB102,311-1080-2-ND,https://www.digikey.com/en/products/detail/yageo/CC0603KRX7R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,,
1,C2,10u 25V,C_0805_2012Metric,Yageo CC0805KKX5R8BB106,311-1869-2-ND,https://www.digikey.com/en/products/detail/yageo/CC0805KKX5R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,U1 input cap,
1,C3,22u 10V tant,CP_EIA-3216-18_Kemet-A,KYOCERA AVX TAJA226K010RNJ,478-1663-2-ND,https://www.digikey.com/en/products/detail/kyocera-avx/TAJA2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,U1 output cap; tantalum per AMS1117 datasheet stability note,
1,D2,SS54,D_SMB,Shenzhen Slkormicro Semicon SS54B,5399-SS54BCT-ND,https://www.digikey.com/en/products/detail/shenzhen-slkormic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,Schottky now (reverse-polarity block); was SMBJ13A TVS,
4,D4 D5 D6 D7,SS34,D_SMA,SMC Diode Solutions SS34AF,1655-SS34AFTR-ND,https://www.digikey.com/en/products/detail/smc-diode-solutio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,,
4,D8 D9 D10 D11,BAT54S,SOT-23,"Nexperia BAT54S,215",1727-2904-2-ND,https://www.digikey.com/en/products/detail/nexperia-usa-inc/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,,
2,D1 D3,1N4148WT,D_SOD-523,SMC Diode Solutions 1N4148WT,1655-1N4148WTTR-ND,https://www.digikey.com/en/products/detail/smc-diode-solutio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,,
1,F1,2.5A,Fuse_1812_4532Metric,Bourns MF-MSMF250/16X-2,MF-MSMF250/16X-2TR-ND,https://www.digikey.com/en/products/detail/bourns-inc/MF-MSM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,,
1,J1,12V IN,ConnHeader_MateNLok_1x04_P5.08mm_Vertical,On-Shore Technology OSTOQ045450,ED2845-ND,https://www.digikey.com/en/products/detail/on-shore-technolo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,,
1,J2,BluePill A,PinSocket_1x20_P2.54mm_Vertical,Sullins PPTC201LFBN-RC,S7018-ND,https://www.digikey.com/en/products/detail/sullins-connector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,,
1,J3,BluePill B,PinSocket_1x20_P2.54mm_Vertical,Sullins PPTC201LFBN-RC,S7018-ND,https://www.digikey.com/en/products/detail/sullins-connector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,,
1,J4,FAN1,FanPinHeader_1x04_P2.54mm_Vertical,Molex 47053-1000,WM4330-ND,https://www.digikey.com/en/products/detail/molex/0470531000/2421261,,
1,J5,FAN2,FanPinHeader_1x04_P2.54mm_Vertical,Molex 47053-1000,WM4330-ND,https://www.digikey.com/en/products/detail/molex/0470531000/2421261,,
1,J6,FAN3,FanPinHeader_1x04_P2.54mm_Vertical,Molex 47053-1000,WM4330-ND,https://www.digikey.com/en/products/detail/molex/0470531000/2421261,,
1,J7,FAN4,FanPinHeader_1x04_P2.54mm_Vertical,Molex 47053-1000,WM4330-ND,https://www.digikey.com/en/products/detail/molex/0470531000/2421261,,
1,J8,AIN3,JST_PH_B2B-PH-K_1x02_P2.00mm_Vertical,JST Sales America B2B-PH-K-S,455-1704-ND,https://www.digikey.com/en/products/detail/jst-sales-america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,Now 2-pin JST-PH; was 3-pin 2.54mm header,
1,J9,AIN4,JST_PH_B2B-PH-K_1x02_P2.00mm_Vertical,JST Sales America B2B-PH-K-S,455-1704-ND,https://www.digikey.com/en/products/detail/jst-sales-america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,Now 2-pin JST-PH; was 3-pin 2.54mm header,
1,J10,AIN1,JST_PH_B2B-PH-K_1x02_P2.00mm_Vertical,JST Sales America B2B-PH-K-S,455-1704-ND,https://www.digikey.com/en/products/detail/jst-sales-america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,Now 2-pin JST-PH; was 3-pin 2.54mm header,
1,J11,AIN2,JST_PH_B2B-PH-K_1x02_P2.00mm_Vertical,JST Sales America B2B-PH-K-S,455-1704-ND,https://www.digikey.com/en/products/detail/jst-sales-america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,Now 2-pin JST-PH; was 3-pin 2.54mm header,
1,LED1,Red,LED_0603_1608Metric,Lite-On LTST-C191KRKT,160-1447-2-ND,https://www.digikey.com/en/products/detail/liteon/LTST-C191K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,,
8,Q1 Q2 Q5 Q6 Q11 Q12 Q17 Q18,AO3401A,SOT-23,Alpha & Omega AO3401A,785-1001-2-ND,https://www.digikey.com/en/products/detail/alpha-omega-semic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,Not MMBT3906 - that part is no longer used,
12,Q3 Q4 Q7 Q8 Q9 Q10 Q13 Q14 Q15 Q16 Q19 Q20,BSS138,SOT-23,MCC BSS138-TP,BSS138-TPMSTR-ND,https://www.digikey.com/en/products/detail/mcc-micro-commerc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,,
18,R1 R4 R8 R9 R10 R16 R17 R21 R25 R26 R30 R34 R37 R39 R41 R42 R43 R44,10k,R_0603_1608Metric,Vishay Dale CRCW060310K0FKEA,541-10.0KHTR-ND,https://www.digikey.com/en/products/detail/vishay-dale/CRCW0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,,
1,R2,3.3k,R_0603_1608Metric,Vishay Dale CRCW06033K30FKEA,541-3.30KHTR-ND,https://www.digikey.com/en/products/detail/vishay-dale/CRCW0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,,
4,R5 R14 R23 R40,4.7k,R_0603_1608Metric,Yageo RC0603FR-074K7L,311-4.70KHRTR-ND,https://www.digikey.com/en/products/detail/yageo/RC0603FR-07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,,
8,R6 R12 R15 R19 R27 R28 R33 R35,100,R_0603_1608Metric,Vishay Dale CRCW0603100RFKEA,541-100HTR-ND,https://www.digikey.com/en/products/detail/vishay-dale/CRCW0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,,
4,R7 R18 R24 R32,2.2k,R_0603_1608Metric,Yageo RC0603FR-072K2L,311-2.20KHRTR-ND,https://www.digikey.com/en/products/detail/yageo/RC0603FR-07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,,
8,R11 R22 R31 R38 R45 R46 R47 R48,1k,R_0603_1608Metric,Vishay Dale CRCW06031K00FKEA,541-1.00KHTR-ND,https://www.digikey.com/en/products/detail/vishay-dale/CRCW0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,,
4,R13 R20 R29 R36,100k,R_0603_1608Metric,Vishay Dale CRCW0603100KFKEA,541-100KHTR-ND,https://www.digikey.com/en/products/detail/vishay-dale/CRCW0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,,
1,R3,4.7k,R_1206_3216Metric,Yageo RC1206FR-074K7L,311-4.70KFRTR-ND,https://www.digikey.com/en/products/detail/yageo/RC1206FR-07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,,
1,U1,AMS1117-3.3,SOT-223-3_TabPin2,Diodes Incorporated AZ1117CH-3.3TRG1,AZ1117CH-3.3TRG1DITR-ND,https://www.digikey.com/en/products/detail/diodes-incorporat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,3.3 V LDO from +12V; any SOT-223 1117-3.3 with GND/OUT/IN pinout fits,

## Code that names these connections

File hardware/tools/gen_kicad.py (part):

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def two_pin(a="~", b="~"):
    return dict(left=[("1", a)], right=[("2", b)], w=2 * G, names=a != "~")

BLUEPILL_A = ["GND", "GND", "3V3", "NRST", "PB11", "PB10", "PB1", "PB0", "PA7", "PA6",
              "PA5", "PA4", "PA3", "PA2", "PA1", "PA0", "PC15", "PC14", "PC13", "VBAT"]
BLUEPILL_B = ["PB12", "PB13", "PB14", "PB15", "PA8", "PA9", "PA10", "PA11", "PA12", "PA15",
              "PB3", "PB4", "PB5", "PB6", "PB7", "PB8", "PB9", "5V", "GND", "3V3"]

SYMBOLS = {
    "R": two_pin(),
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B = "MCU"
bluepill = {
    "GND": "GND", "3V3": "+3V3", "5V": "+5V", "NRST": "NRST",
    "PA0": "AIN1", "PA1": "AIN2", "PA2": "AIN3", "PA3": "AIN4", "PA4": "AIN5", "PA5": "AIN6",
    "PB0": "V12_SENSE", "PA11": "USB_DM", "PA12": "USB_DP",
    "PB6": "FAN1_PWM", "PB7": "FAN2_PWM", "PB8": "FAN3_PWM", "PB9": "FAN4_PWM",
    "PB12": "FAN1_TACH", "PB13": "FAN2_TACH", "PB14": "FAN3_TACH", "PB15": "FAN4_TACH",
}
for row, names in (("A", BLUEPILL_A), ("B", BLUEPILL_B)):
    part(B, f"BluePill_{row}", f"BluePill {row}", FP_SOCKET20,
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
